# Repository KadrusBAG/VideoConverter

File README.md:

# VideoConverter
Video converter VGA, DVI-I, HDMI to RCA

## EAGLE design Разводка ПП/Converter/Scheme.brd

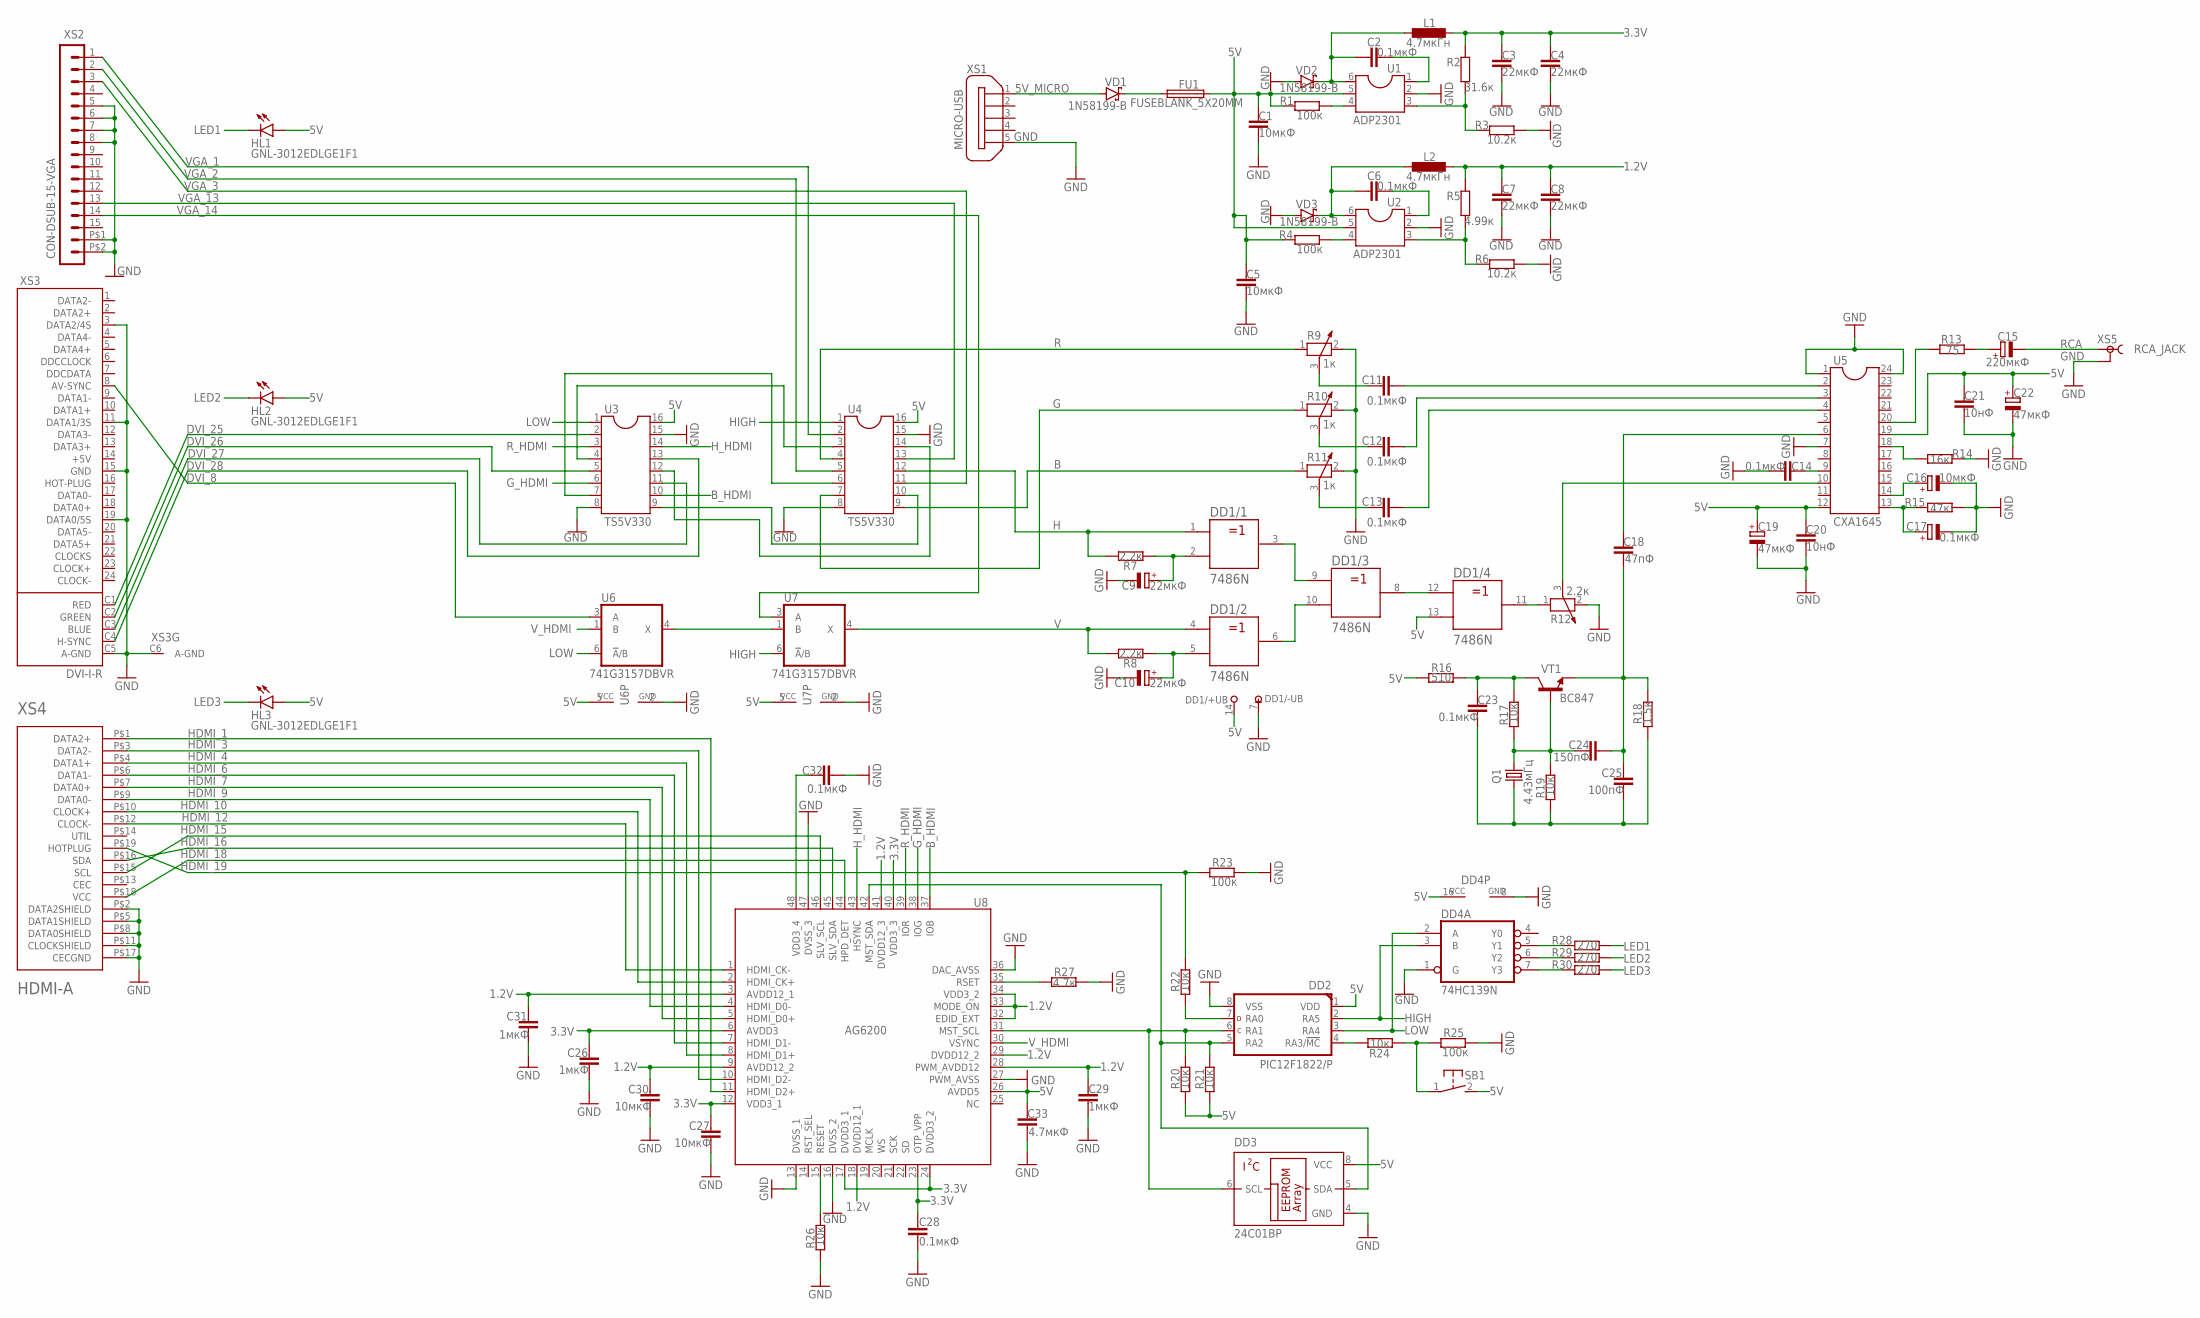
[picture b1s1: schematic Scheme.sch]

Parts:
C1, C5, C27, C30: 10мкФ; C0603
C2, C6, C11, C12, C13, C14, C23, C28, C32: 0.1мкФ; C1206
C3, C4, C7, C8: 22мкФ; C1206
C9, C10: 22мкФ; E2,5-6E
C15: 220мкФ; E2,5-6E
C16: 10мкФ; E2,5-6E
C17: 0.1мкФ; E2,5-6E
C18: 47пФ; C0603
C19, C22: 47мкФ; E2,5-6E
C20, C21: 10нФ; C0603
C24: 150пФ; C0805
C25: 100пФ; C0805
C26, C29, C31: 1мкФ; C0603
C33: 4.7мкФ; C0805
DD1: 7486N; DIL14
DD2: PIC12F1822/P; DIL8-P
DD3: 24C01BP; DIL8
DD4: 74HC139N; DIL16
FU1: FUSEBLANK_5X20MM; FUSE_HOLDER_5X20MM
HL1, HL2, HL3: GNL-3012EDLGE1F1; PLCC2
L1, L2: 4.7мкГн; PIS2816
Q1: 4.43мГц; HC49U-V
R1, R4, R23, R25: 100к; R2512
R2: 31.6к; R0805
R3, R6: 10.2к; R0805
R5: 4.99к; R0805
R7, R8: 2.2к; R0402
R9, R10, R11: 1к; PT-10
R12: 2.2к; PT-10
R13: 75; R0402
R14: 16к; R0402
R15: 47к; R0402
R16: 510; R0402
R17, R19, R20, R21, R22, R24, R26: 10к; R0805
R18: 1.5к; R0402
R27: 4.7к; R0402
R28, R29, R30: 270; R0402
SB1: 31-XX; B3F-31XX
U1, U2: ADP2301; DIL06
U3, U4: TS5V330; DIL16
U5: CXA1645; DIL24-4
U6, U7: 741G3157DBVR; DBV_R-PDSO-G6
U8: AG6200; PLCC-48
VD1, VD2, VD3: 1N58199-B; DO41-7.6
VT1: BC847; SOT23-BEC
XS1: MICRO-USB; ZX62D-B-5PA8
XS2: CON-DSUB-15-VGA; 181-015-212-171
XS3: DVI-I-R
XS4: HDMI-A; HDMI_A
XS5: RCA_JACK; TOBU3

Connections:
1.2V: C7.1, C8.1, C29.1, C30.1, C31.1, L2.2, R5.2, U8.3 (AVDD12_1), U8.9 (AVDD12_2), U8.18 (DVDD12_1), U8.28 (PWM_AVDD12), U8.29 (DVDD12_2), U8.32 (EDID_EXT), U8.33 (MODE_ON), U8.34 (VDD3_2), U8.41 (DVDD12_3)
3.3V: C3.1, C4.1, C26.1, C27.1, C28.1, L1.2, R2.2, U8.6 (AVDD3), U8.12 (VDD3_1), U8.17 (DVDD3_1), U8.23 (OTP_VPP), U8.24 (DVDD3_2), U8.40 (VDD3_3)
5V: C1.1, C5.1, C19.+, C20.1, C21.1, C22.+, C33.1, DD1.13 (B), DD1.14 (+UB), DD2.1 (VDD), DD3.8 (VCC), DD4.16 (VCC), FU1.2, HL1.A, HL2.A, HL3.A, R1.1, R4.1, R16.1, R20.1, R21.1, SB1.2 (S), U1.5, U2.5, U3.16, U4.16, U5.12, U5.19, U6.5 (VCC), U7.5 (VCC), U8.26 (AVDD5)
5V_MICRO: VD1.A, XS1.1
+5V: XS3.14 (+5V)
B: R11.1, U4.9
B_HDMI: U3.10, U8.37 (IOB)
DVI_8: U6.3 (A), XS3.8 (AV-SYNC)
DVI_25: U3.2, XS3.C1 (RED)
DVI_26: U3.5, XS3.C2 (GREEN)
DVI_27: U3.11, XS3.C3 (BLUE)
DVI_28: U3.13, XS3.C4 (H-SYNC)
G: R10.1, U4.7
GND: C1.2, C3.2, C4.2, C5.2, C7.2, C8.2, C9.-, C10.-, C14.2, C16.-, C17.-, C19.-, C20.2, C21.2, C22.-, C26.2, C27.2, C28.2, C29.2, C30.2, C31.2, C32.2, C33.2, DD1.7 (-UB), DD2.8 (VSS), DD3.4 (GND), DD4.1 (G), DD4.8 (GND), R3.1, R6.1, R9.2, R10.2, R11.2, R12.2, R14.2, R15.2, R23.2, R25.2, R26.1, R27.2, U1.2, U2.2, U3.8, U3.15, U4.8, U4.15, U5.1, U5.7, U5.24, U6.2 (GND), U7.2 (GND), U8.13 (DVSS_1), U8.16 (DVSS_2), U8.27 (PWM_AVSS), U8.36 (DAC_AVSS), U8.47 (DVSS_3), VD2.A, VD3.A, XS1.5, XS2.5, XS2.6, XS2.7, XS2.8, XS2.P$1 (16), XS2.P$2 (17), XS3.3 (DATA2/4S), XS3.11 (DATA1/3S), XS3.15 (GND), XS3.19 (DATA0/5S), XS3.C5 (A-GND), XS3.C6 (A-GND), XS4.P$2 (DATA2SHIELD), XS4.P$5 (DATA1SHIELD), XS4.P$8 (DATA0SHIELD), XS4.P$11 (CLOCKSHIELD), XS4.P$17 (CECGND), XS5.2, XS5.2@1 (2), XS5.2@2 (2)
G_HDMI: U3.6, U8.38 (IOG)
H: DD1.1 (A), R7.1, U4.12
HDMI_1: U8.11 (HDMI_D2+), XS4.P$1 (DATA2+)
HDMI_3: U8.10 (HDMI_D2-), XS4.P$3 (DATA2-)
HDMI_4: U8.8 (HDMI_D1+), XS4.P$4 (DATA1+)
HDMI_6: U8.7 (HDMI_D1-), XS4.P$6 (DATA1-)
HDMI_7: U8.5 (HDMI_D0+), XS4.P$7 (DATA0+)
HDMI_9: U8.4 (HDMI_D0-), XS4.P$9 (DATA0-)
HDMI_10: U8.2 (HDMI_CK+), XS4.P$10 (CLOCK+)
HDMI_12: U8.1 (HDMI_CK-), XS4.P$12 (CLOCK-)
HDMI_15: U8.46 (SLV_SCL), XS4.P$15 (SCL)
HDMI_16: U8.45 (SLV_SDA), XS4.P$16 (SDA)
HDMI_18: U8.44 (HPD_DET), XS4.P$18 (VCC)
HDMI_19: R22.2, R23.1, XS4.P$19 (HOTPLUG)
HIGH: DD2.2 (RA5), DD4.3 (B), U4.1, U7.6 (!A!/B)
H_HDMI: U3.14, U8.43 (HSYNC)
LED1: HL1.C, R28.2
LED2: HL2.C, R29.2
LED3: HL3.C, R30.2
LOW: DD2.3 (RA4), DD4.2 (A), U3.1, U6.6 (!A!/B)
unnamed: FU1.1, VD1.C
unnamed: C9.+, DD1.2 (B), R7.2
unnamed: C2.1, L1.1, U1.6, VD2.C
unnamed: C10.+, DD1.5 (B), R8.2
unnamed: C2.2, U1.1
unnamed: R2.1, R3.2, U1.3
unnamed: R1.2, U1.4
unnamed: C6.1, L2.1, U2.6, VD3.C
unnamed: C6.2, U2.1
unnamed: R5.1, R6.2, U2.3
unnamed: DD4.5 (Y1), R28.1
unnamed: R4.2, U2.4
unnamed: C11.2, U5.2
unnamed: DD1.3 (Y), DD1.9 (A)
unnamed: DD1.6 (Y), DD1.10 (B)
unnamed: C12.2, U5.3
unnamed: DD1.8 (Y), DD1.12 (A)
unnamed: DD1.11 (Y), R12.1
unnamed: C11.1, R9.3
unnamed: C12.1, R10.3
unnamed: C13.1, R11.3
unnamed: C13.2, U5.4
unnamed: R12.3, U5.10
unnamed: C23.1, R16.2, R17.2, VT1.C
unnamed: C23.2, C25.2, Q1.2, R18.1, R19.1
unnamed: C24.1, Q1.1, R17.1, R19.2, VT1.B
unnamed: C18.2, C24.2, C25.1, R18.2, VT1.E
unnamed: C18.1, U5.6
unnamed: DD4.6 (Y2), R29.1
unnamed: C14.1, U5.9
unnamed: DD4.7 (Y3), R30.1
unnamed: C17.+, R15.1, U5.13
unnamed: C16.+, U5.14
unnamed: R14.1, U5.18
unnamed: R13.1, U5.20
unnamed: U6.4 (X), U7.1 (B)
unnamed: C15.+, R13.2
unnamed: U3.4, U4.3
unnamed: U3.7, U4.6
unnamed: U3.9, U4.10
unnamed: C32.1, U8.48 (VDD3_4)
unnamed: U3.12, U4.14
unnamed: R26.2, U8.15 (RESET)
unnamed: R27.1, U8.35 (RSET)
unnamed: DD2.6 (RA1), DD3.6 (SCL), R20.2, U8.31 (MST_SCL)
unnamed: DD2.5 (RA2), DD3.5 (SDA), R21.2, U8.42 (MST_SDA)
unnamed: DD2.7 (RA0), R22.1
unnamed: DD2.4 (RA3/!MC!), R24.2
unnamed: R24.1, R25.1, SB1.1
R: R9.1, U4.4
RCA: C15.-, XS5.1
R_HDMI: U3.3, U8.39 (IOR)
V: DD1.4 (A), R8.1, U7.4 (X)
VGA_1: U4.2, XS2.1
VGA_2: U4.5, XS2.2
VGA_3: U4.11, XS2.3
VGA_13: U4.13, XS2.13
VGA_14: U7.3 (A), XS2.14
V_HDMI: U6.1 (B), U8.30 (VSYNC)

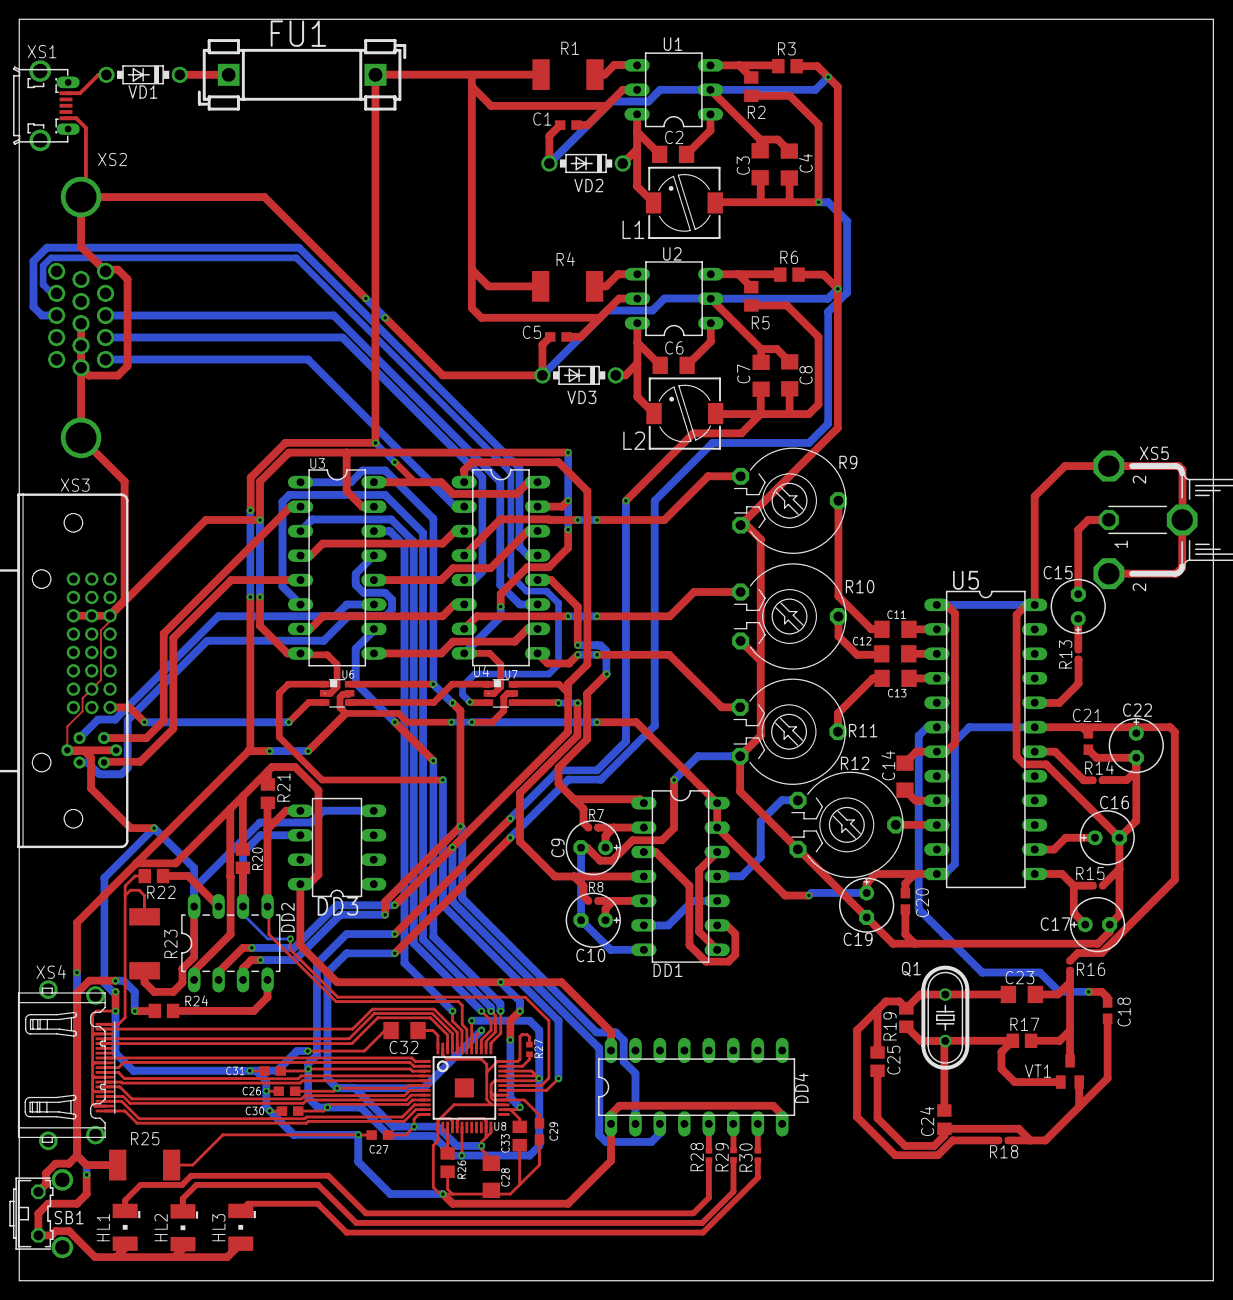
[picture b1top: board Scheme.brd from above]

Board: 2 copper layers, 124.0 x 131.0 mm, 92 parts (0 on the bottom side), 92 nets.
